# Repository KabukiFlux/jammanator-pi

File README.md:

# Raspberry pi jamma bard "jammanator"

<b align="center">Jammanator, the Raspberry Pi JAMMA output board 
for your cabinet</b>

## Table of contents

- [Why](#why)
- [Description](#description)
- [Schematics](#schematics)
- [Install](#install)
- [Pics and final result](#pics-and-final-result)

## Why?

This was done during some live events on Twitch.tv and tested for some time.

This is a very old design for Raspberry Pi 3B+, 4, 400, it no longer 
has the status that anybody can make money and make profit of it 
so I decided to publish it, if you have an arcade cabinet with JAMMA
a spare Raspberry Pi 3B+ or 4 and you want to have something running
then is a matter of burning the rgbpiOS or the recalboxOS and you have
everything you need to make it work.

## Description

This board is intended to be a PCB used with a Raspberry Pi and a 4x4 5v fan
to remove some heat from the CPU.

This board uses 2 I2C parallel expansion I/O chips connected to the JAMMA
connector in order to map automatically the buttons to the cabinet with no
configuration required.

A voltmeter has been added to check the 5v rail while running.

A protection circuit has been mapped to all the inputs and an extra buffer
to avoid any loss of the I2C bus, if the I2C bus is lost the Raspberry will 
no longer boot the OS (yellow led) this design will avoid that.

In the BOM directory there's an interactive BOM with all the required components.

In the gerbers directory we have the gerbers to manufacture the boards.

In the KiCAD folder we can find the KiCAD project itself.

In the circuit_js folder you can find the simulation for the I/O protection.

## Schematics

This is the schematics.

## Install

If you use a Raspberry Pi 400 (the one with the keyboard) I recommend this
board and the extender in order to use it (check carefully the connector position):

- [GPIO board](https://www.amazon.es/IBest-Waveshare-Raspberry-Color-Coded-Expansion/dp/B08SK71PB4)

- [Extension cable](https://www.amazon.es/vhbw-extensi%C3%B3n-compatible-Raspberry-miniordenador/dp/B0B94KRZ8Z)

Ensure the RP400 pin is in the right position, as the RP400 cannot be powered
via the GPIO we must provide USB-C power and avoid sending power to the GPIO.

1- Send to manufacture the GERBER board to [JLCPCB](https://jlcpcb.com/) or other PCB manufacturer.

2- Get the components required, you can see here the Bill Of Materials [BOM](bom/ibom.html)

3- Solder the components.

4- Connect a Raspberry Pi with [rgbpi-OS](https://ko-fi.com/s/4119fb48b8) or 
[recalbox-OS](https://www.recalbox.com/es/download/stable/rpi/)

5- Follow the installation guide and instructions for the selected OS. 

Once finished you should have something like this:

### Pics and final result

I'm not responsible
============
And yes, read below, no liability is assumed for misuse.

DISCLAIMER (See Licensing)
==========================
See LICENSE fo more information.

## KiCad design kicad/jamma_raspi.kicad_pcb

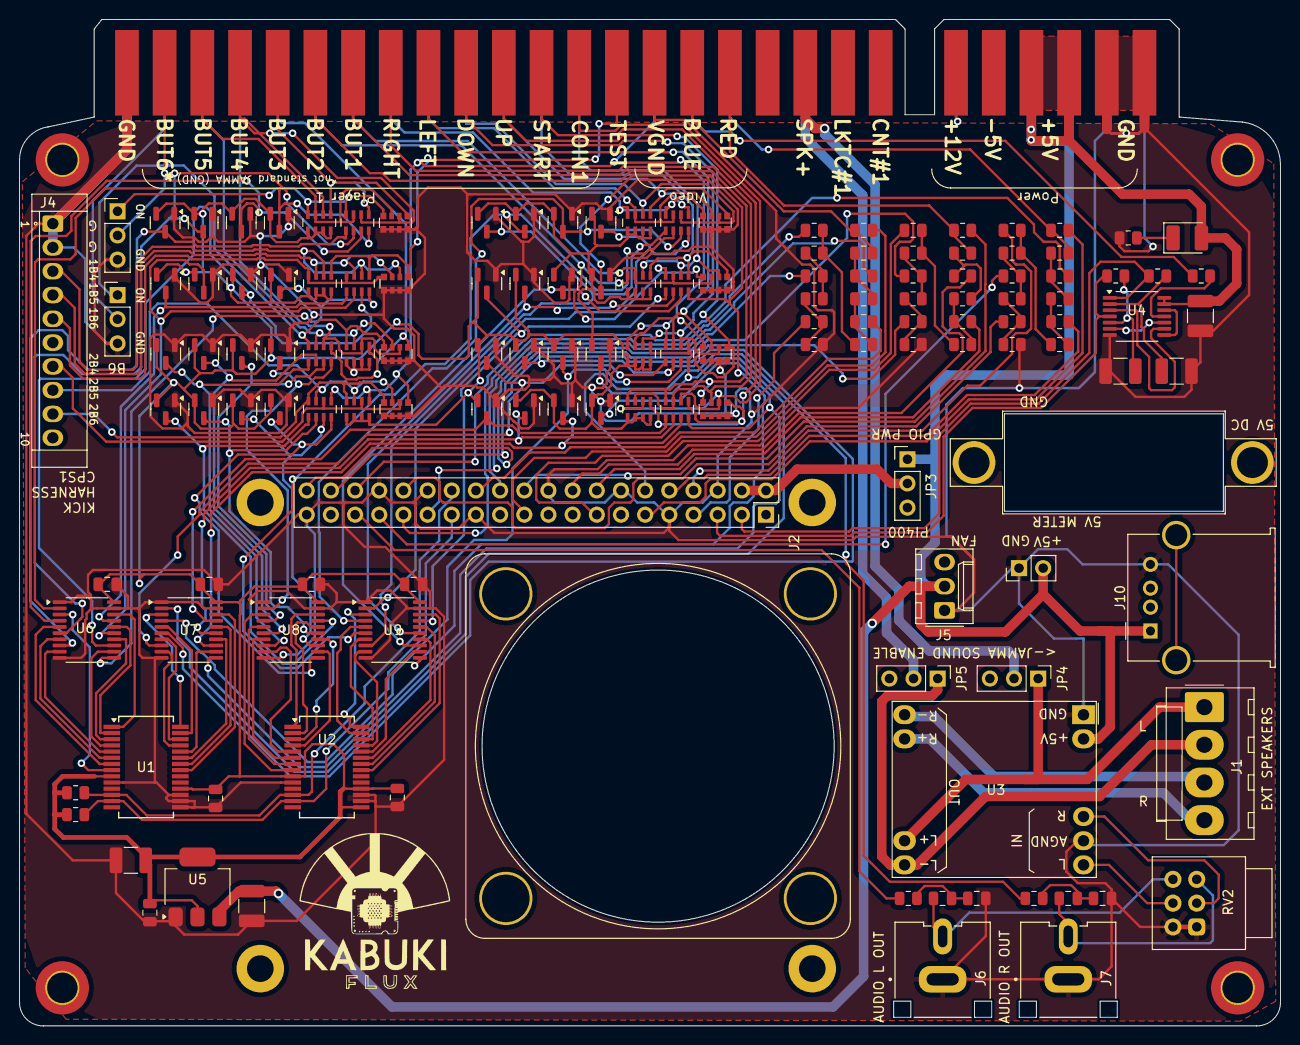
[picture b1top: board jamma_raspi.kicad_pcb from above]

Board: 2 copper layers, 132.5 x 105.7 mm, 149 parts (1 on the bottom side), 165 nets.

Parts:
C1, C4, C16, C17, C18, C50, C51, C52, C53: 0.1u; C_0805_2012Metric
C2, C3: 470n; C_0805_2012Metric
C10, C11, C12, C13, C15: 10u; C_1210_3225Metric_Pad1.33x2.70mm_HandSolder
CN1, CN2, CN3, CN4, CN5, CN6, CN7, CN8: 100n; C_Array_Convex_4x0612
D1, D2, D3, D4, D5, D6, D7, D8, D9, D10, D11, D12, D13, D14, D15, D16, D17, D18, D19, D20, D21, D22, D23, D24, D25, D26, D27, D28, D29, D30, D31, D32: BAT54S; SOT-23
DPWR1: LED RED; LED_1210_3225Metric_Pad1.42x2.65mm_HandSolder
FAN1: Noctua_NF-A4x10_40mm
G1: LOGO; LogoKabuki_18mm
G2: LOGO; LogoKabuki
J1: SPEAKER_STEREO MOLEX396; Molex_KK-396_A-41791-0004_1x04_P3.96mm_Vertical
J2: CONN_02X20; GPIO_2x20_P2.54mm_Vertical_Tall_w_Standoffs
J3: JAMMA_edge
J4: Kick Harness (CPS1 pinout); B10P-SHF-1AA
J5: FAN_5v; Molex_KK-254_AE-6410-03A_1x03_P2.54mm_Vertical
J6: AUDIO L OUT; CUI_RCJ-043
J7: AUDIO R OUT; CUI_RCJ-043
J10: RP400_USB; USB_A_Molex_67643_Horizontal
JP1: 1P_B6_CHAMMA_JAMMA; PinHeader_1x03_P2.54mm_Vertical
JP2: 2P_B6_CHAMMA_JAMMA; PinHeader_1x03_P2.54mm_Vertical
JP3: PI_400_DISCONNECT; PinHeader_1x03_P2.54mm_Vertical
JP4: JAMMA_SPK_DIS_+; PinHeader_1x03_P2.54mm_Vertical
JP5: JAMMA_SPK_DIS_-; PinHeader_1x03_P2.54mm_Vertical
M1, M2, M3, M4: MountingHole_3.2mm_M3_DIN965_Pad_TopBottom
MES1: Voltmeter_DC; PinHeader_1x02_P2.54mm_Vertical
RB1, RB2, RB3, RB4, RB5, RB6: 475; R_0805_2012Metric
RB7, RB8, RB9, RB10, RB11, RB12: 240; R_0805_2012Metric
RG1, RG2, RG3, RG4, RG5, RG6: 475; R_0805_2012Metric
RG7, RG8, RG9, RG10, RG11, RG12: 240; R_0805_2012Metric
RI2C1, RI2C2: 10k; R_0805_2012Metric
RLED1: 1k; R_0805_2012Metric
RN1, RN3, RN5, RN7, RN9, RN11, RN13, RN15: 1k; R_Array_Concave_4x0603
RN2, RN4, RN6, RN8, RN10, RN12, RN14, RN16: 10k; R_Array_Concave_4x0603
RPWM1, RPWM2: 220; R_0805_2012Metric
RR1, RR2, RR3, RR4, RR5, RR6: 475; R_0805_2012Metric
RR7, RR8, RR9, RR10, RR11, RR12: 240; R_0805_2012Metric
RS1, RS2: 4k7; R_0805_2012Metric
RS3: 100; R_0805_2012Metric
RV2: 10k; Potentiometer_Alps_RK097_Dual_Horizontal
U1: MCP23017_SO_PLAYER1; SSOP-28_5.3x10.2mm_P0.65mm
U2: MCP23017_SO_PLAYER2; SSOP-28_5.3x10.2mm_P0.65mm
U3: PAM8403 PCB; PAM8403_module
U4: 74HC86; TSSOP-14_4.4x5mm_P0.65mm
U5: LM1117IMPX-3.3/NOPB; SOT-223-3_TabPin2
U6, U7, U8, U9: SN74LVC244APWR; TSSOP-20_4.4x6.5mm_P0.65mm
VM1: Voltmeter Mechanical; voltmeter

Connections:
+3.3V: C15.1, C16.1, C17.1, C18.1, C50.1, C51.1, C52.1, C53.1, D1.2 (K), D2.2 (K), D3.2 (K), D4.2 (K), D5.2 (K), D6.2 (K), D7.2 (K), D8.2 (K), D9.2 (K), D10.2 (K), D11.2 (K), D12.2 (K), D13.2 (K), D14.2 (K), D15.2 (K), D16.2 (K), D17.2 (K), D18.2 (K), D19.2 (K), D20.2 (K), D21.2 (K), D22.2 (K), D23.2 (K), D24.2 (K), D25.2 (K), D26.2 (K), D27.2 (K), D28.2 (K), D29.2 (K), D30.2 (K), D31.2 (K), D32.2 (K), RI2C1.1, RI2C2.1, RN2.5 (R4.2), RN2.6 (R3.2), RN2.7 (R2.2), RN2.8 (R1.2), RN4.5 (R4.2), RN4.6 (R3.2), RN4.7 (R2.2), RN4.8 (R1.2), RN6.5 (R4.2), RN6.6 (R3.2), RN6.7 (R2.2), RN6.8 (R1.2), RN8.5 (R4.2), RN8.6 (R3.2), RN8.7 (R2.2), RN8.8 (R1.2), RN10.5 (R4.2), RN10.6 (R3.2), RN10.7 (R2.2), RN10.8 (R1.2), RN12.5 (R4.2), RN12.6 (R3.2), RN12.7 (R2.2), RN12.8 (R1.2), RN14.5 (R4.2), RN14.6 (R3.2), RN14.7 (R2.2), RN14.8 (R1.2), RN16.5 (R4.2), RN16.6 (R3.2), RN16.7 (R2.2), RN16.8 (R1.2), U1.9 (VDD), U1.18 (~RESET), U2.9 (VDD), U2.15 (A0), U2.18 (~RESET), U5.2 (VO), U6.20 (VCC), U7.20 (VCC), U8.20 (VCC), U9.20 (VCC)
+5V: C12.1, C13.1, DPWR1.2 (A), J3.3 (+5V), J3.4 (+5V), J3.C (+5V), J3.D (+5V), J5.2, J10.1 (VBUS), JP3.1 (A), MES1.2 (+), U3.2 (VCC), U4.13, U4.14 (VCC), U5.3 (VI)
+12V: J3.6 (+12V), J3.F (+12V)
/B2: J2.7, RB6.1
/B3: J2.29, RB5.1
/B4: J2.31, RB4.1
/B5: J2.26, RB3.1
/B6: J2.24, RB2.1
/B7: J2.21, RB1.1
/BLANKING: U4.8, U4.12
/CSYNC: J3.P (Video_Sync), RS3.1
/G2: J2.32, RG6.1
/G3: J2.33, RG5.1
/G4: J2.8, RG4.1
/G5: J2.10, RG3.1
/G6: J2.36, RG2.1
/G7: J2.11, RG1.1
/HSYNC: J2.5, RS2.2, U4.4
/I2C_SCL: J2.28, RI2C2.2, U1.12 (SCK), U2.12 (SCK)
/I2C_SDA: J2.27, RI2C1.2, U1.13 (SDA), U2.13 (SDA)
/JAMMA RASPI IOs/INPUT01: D1.3 (COM), RN1.8 (R1.2), U6.2 (I0a)
/JAMMA RASPI IOs/INPUT02: D2.3 (COM), RN1.7 (R2.2), U6.4 (I1a)
/JAMMA RASPI IOs/INPUT03: D3.3 (COM), RN1.6 (R3.2), U6.6 (I2a)
/JAMMA RASPI IOs/INPUT04: D4.3 (COM), RN1.5 (R4.2), U6.8 (I3a)
/JAMMA RASPI IOs/INPUT05: D5.3 (COM), RN3.8 (R1.2), U6.11 (I0b)
/JAMMA RASPI IOs/INPUT06: D6.3 (COM), RN3.7 (R2.2), U6.13 (I1b)
/JAMMA RASPI IOs/INPUT07: D7.3 (COM), RN3.6 (R3.2), U6.15 (I2b)
/JAMMA RASPI IOs/INPUT08: D8.3 (COM), RN3.5 (R4.2), U6.17 (I3b)
/JAMMA RASPI IOs/INPUT11: D9.3 (COM), RN5.8 (R1.2), U7.2 (I0a)
/JAMMA RASPI IOs/INPUT12: D10.3 (COM), RN5.7 (R2.2), U7.4 (I1a)
/JAMMA RASPI IOs/INPUT13: D11.3 (COM), RN5.6 (R3.2), U7.6 (I2a)
/JAMMA RASPI IOs/INPUT14: D12.3 (COM), RN5.5 (R4.2), U7.8 (I3a)
/JAMMA RASPI IOs/INPUT15: D13.3 (COM), RN7.8 (R1.2), U7.11 (I0b)
/JAMMA RASPI IOs/INPUT16: D14.3 (COM), RN7.7 (R2.2), U7.13 (I1b)
/JAMMA RASPI IOs/INPUT17: D15.3 (COM), RN7.6 (R3.2), U7.15 (I2b)
/JAMMA RASPI IOs/INPUT18: D16.3 (COM), RN7.5 (R4.2), U7.17 (I3b)
/JAMMA RASPI IOs/INPUT21: D17.3 (COM), RN9.8 (R1.2), U8.2 (I0a)
/JAMMA RASPI IOs/INPUT22: D18.3 (COM), RN9.7 (R2.2), U8.4 (I1a)
/JAMMA RASPI IOs/INPUT23: D19.3 (COM), RN9.6 (R3.2), U8.6 (I2a)
/JAMMA RASPI IOs/INPUT24: D20.3 (COM), RN9.5 (R4.2), U8.8 (I3a)
/JAMMA RASPI IOs/INPUT25: D21.3 (COM), RN11.8 (R1.2), U8.11 (I0b)
/JAMMA RASPI IOs/INPUT26: D22.3 (COM), RN11.7 (R2.2), U8.13 (I1b)
/JAMMA RASPI IOs/INPUT27: D23.3 (COM), RN11.6 (R3.2), U8.15 (I2b)
/JAMMA RASPI IOs/INPUT28: D24.3 (COM), RN11.5 (R4.2), U8.17 (I3b)
/JAMMA RASPI IOs/INPUT31: D25.3 (COM), RN13.8 (R1.2), U9.2 (I0a)
/JAMMA RASPI IOs/INPUT32: D26.3 (COM), RN13.7 (R2.2), U9.4 (I1a)
/JAMMA RASPI IOs/INPUT33: D27.3 (COM), RN13.6 (R3.2), U9.6 (I2a)
/JAMMA RASPI IOs/INPUT34: D28.3 (COM), RN13.5 (R4.2), U9.8 (I3a)
/JAMMA RASPI IOs/INPUT35: D29.3 (COM), RN15.8 (R1.2), U9.11 (I0b)
/JAMMA RASPI IOs/INPUT36: D30.3 (COM), RN15.7 (R2.2), U9.13 (I1b)
/JAMMA RASPI IOs/INPUT37: D31.3 (COM), RN15.6 (R3.2), U9.15 (I2b)
/JAMMA RASPI IOs/INPUT38: D32.3 (COM), RN15.5 (R4.2), U9.17 (I3b)
/L: C2.1, J6.1 (In), RV2.6
/P1_B1: U1.27 (GPA6), U7.5 (O2b)
/P1_B1_J: CN4.3 (R3.1), J3.22 (Player_1_Button_1), RN7.3 (R3.1), RN8.3 (R3.1)
/P1_B2: U1.28 (GPA7), U7.3 (O3b)
/P1_B2_J: CN4.4 (R4.1), J3.23 (Player_1_Button_2), RN7.4 (R4.1), RN8.4 (R4.1)
/P1_B3: U1.1 (GPB0), U6.18 (O0a)
/P1_B3_J: CN1.1 (R1.1), J3.24 (Player_1_Button_3), RN1.1 (R1.1), RN2.1 (R1.1)
/P1_B4: U1.2 (GPB1), U6.16 (O1a)
/P1_B4_J: CN1.2 (R2.1), J3.25 (Player_1_Button_4), RN1.2 (R2.1), RN2.2 (R2.1)
/P1_B5: U1.3 (GPB2), U6.14 (O2a)
/P1_B5_J: CN1.3 (R3.1), J3.26 (Player_1_Button_5), RN1.3 (R3.1), RN2.3 (R3.1)
/P1_B6: U1.4 (GPB3), U6.12 (O3a)
/P1_B6_J: J3.27 (GND/P1_Button_6), JP1.2 (C)
/P1_B6_J_C: CN1.4 (R4.1), JP1.1 (A), RN1.4 (R4.1), RN2.4 (R4.1)
/P1_COIN: U1.26 (GPA5), U7.7 (O1b)
/P1_COIN_J: CN4.2 (R2.1), J3.16 (Coin_1), RN7.2 (R2.1), RN8.2 (R2.1)
/P1_DOWN: U1.22 (GPA1), U7.16 (O1a)
/P1_DOWN_J: CN3.2 (R2.1), J3.19 (Player_1_Down), RN5.2 (R2.1), RN6.2 (R2.1)
/P1_K4: U1.6 (GPB5), U6.7 (O1b)
/P1_K4_K: CN2.2 (R2.1), J4.3, RN3.2 (R2.1), RN4.2 (R2.1)
/P1_K5: U1.7 (GPB6), U6.5 (O2b)
/P1_K5_K: CN2.3 (R3.1), J4.4, RN3.3 (R3.1), RN4.3 (R3.1)
/P1_K6: U1.8 (GPB7), U6.3 (O3b)
/P1_K6_K: CN2.4 (R4.1), J4.5, RN3.4 (R4.1), RN4.4 (R4.1)
/P1_LEFT: U1.23 (GPA2), U7.14 (O2a)
/P1_LEFT_J: CN3.3 (R3.1), J3.20 (Player_1_Left), RN5.3 (R3.1), RN6.3 (R3.1)
/P1_RIGHT: U1.24 (GPA3), U7.12 (O3a)
/P1_RIGHT_J: CN3.4 (R4.1), J3.21 (Player_1_Right), RN5.4 (R4.1), RN6.4 (R4.1)
/P1_START: U1.25 (GPA4), U7.9 (O0b)
/P1_START_J: CN4.1 (R1.1), J3.17 (Player_1_Start), RN7.1 (R1.1), RN8.1 (R1.1)
/P1_UP: U1.21 (GPA0), U7.18 (O0a)
/P1_UP_J: CN3.1 (R1.1), J3.18 (Player_1_Up), RN5.1 (R1.1), RN6.1 (R1.1)
/P2_B1: U2.27 (GPA6), U9.5 (O2b)
/P2_B1_J: CN8.3 (R3.1), J3.Z (Player_2_Button_1), RN15.3 (R3.1), RN16.3 (R3.1)
/P2_B2: U2.28 (GPA7), U9.3 (O3b)
/P2_B2_J: CN8.4 (R4.1), J3.a (Player_2_Button_2), RN15.4 (R4.1), RN16.4 (R4.1)
/P2_B3: U2.1 (GPB0), U8.18 (O0a)
/P2_B3_J: CN5.1 (R1.1), J3.b (Player_2_Button_3), RN9.1 (R1.1), RN10.1 (R1.1)
/P2_B4: U2.2 (GPB1), U8.16 (O1a)
/P2_B4_J: CN5.2 (R2.1), J3.c (Player_2_Button_4), RN9.2 (R2.1), RN10.2 (R2.1)
/P2_B5: U2.3 (GPB2), U8.14 (O2a)
/P2_B5_J: CN5.3 (R3.1), J3.d (Player_2_Button_5), RN9.3 (R3.1), RN10.3 (R3.1)
/P2_B6: U2.4 (GPB3), U8.12 (O3a)
/P2_B6_J: J3.e (GND/P2_Button_6), JP2.2 (C)
/P2_B6_J_C: CN5.4 (R4.1), JP2.1 (A), RN9.4 (R4.1), RN10.4 (R4.1)
/P2_COIN: U2.26 (GPA5), U9.7 (O1b)
/P2_COIN_J: CN8.2 (R2.1), J3.T (Coin_2), RN15.2 (R2.1), RN16.2 (R2.1)
/P2_DOWN: U2.22 (GPA1), U9.16 (O1a)
/P2_DOWN_J: CN7.2 (R2.1), J3.W (Player_2_Down), RN13.2 (R2.1), RN14.2 (R2.1)
/P2_K4: U2.6 (GPB5), U8.7 (O1b)
/P2_K4_K: CN6.2 (R2.1), J4.7, RN11.2 (R2.1), RN12.2 (R2.1)
/P2_K5: U2.7 (GPB6), U8.5 (O2b)
/P2_K5_K: CN6.3 (R3.1), J4.8, RN11.3 (R3.1), RN12.3 (R3.1)
/P2_K6: U2.8 (GPB7), U8.3 (O3b)
/P2_K6_K: CN6.4 (R4.1), J4.9, RN11.4 (R4.1), RN12.4 (R4.1)
/P2_LEFT: U2.23 (GPA2), U9.14 (O2a)
/P2_LEFT_J: CN7.3 (R3.1), J3.X (Player_2_Left), RN13.3 (R3.1), RN14.3 (R3.1)
/P2_RIGHT: U2.24 (GPA3), U9.12 (O3a)
/P2_RIGHT_J: CN7.4 (R4.1), J3.Y (Player_2_Right), RN13.4 (R4.1), RN14.4 (R4.1)
/P2_START: U2.25 (GPA4), U9.9 (O0b)
/P2_START_J: CN8.1 (R1.1), J3.U (Player_2_Start), RN15.1 (R1.1), RN16.1 (R1.1)
/P2_UP: U2.21 (GPA0), U9.18 (O0a)
/P2_UP_J: CN7.1 (R1.1), J3.V (Player_2_Up), RN13.1 (R1.1), RN14.1 (R1.1)
/PI_PWR: J2.2, J2.4, JP3.2 (C)
/PWM_LEFT: J2.35, RPWM2.1
/PWM_RIGHT: J2.12, RPWM1.1
/R: C3.1, J7.1 (In), RV2.3
/R2: J2.38, RR6.1
/R3: J2.40, RR5.1
/R4: J2.15, RR4.1
/R5: J2.16, RR3.1
/R6: J2.18, RR2.1
/R7: J2.22, RR1.1
/RGB_BLUE: J3.13 (Video_Blue), RB1.2, RB12.1
/RGB_GREEN: J3.N (Video_Green), RG1.2, RG12.1
/RGB_RED: J3.12 (Video_Red), RR1.2, RR12.1
/SERVICE: U2.5 (GPB4), U8.9 (O0b)
/SERVICE_J: CN6.1 (R1.1), J3.R (Service), RN11.1 (R1.1), RN12.1 (R1.1)
/SPK_L+: J1.1, JP4.1 (A), U3.7 (L_OUT+)
/SPK_L+_J: J3.10 (Speaker+/R), JP4.2 (C)
/SPK_L-: J1.2, JP5.1 (A), U3.6 (L_OUT-)
/SPK_L-_J: J3.L (Speaker-/L), JP5.2 (C)
/SPK_R+: J1.4, U3.8 (R_OUT+)
/SPK_R-: J1.3, U3.9 (R_OUT-)
/TEST: U1.5 (GPB4), U6.9 (O0b)
/TEST_J: CN2.1 (R1.1), J3.15 (Test), RN3.1 (R1.1), RN4.1 (R1.1)
/VSYNC: J2.3, RS1.2, U4.1
GND: C1.2, C4.2, C10.2, C11.2, C12.2, C13.2, C15.2, C16.2, C17.2, C18.2, C50.2, C51.2, C52.2, C53.2, CN1.5 (R4.2), CN1.6 (R3.2), CN1.7 (R2.2), CN1.8 (R1.2), CN2.5 (R4.2), CN2.6 (R3.2), CN2.7 (R2.2), CN2.8 (R1.2), CN3.5 (R4.2), CN3.6 (R3.2), CN3.7 (R2.2), CN3.8 (R1.2), CN4.5 (R4.2), CN4.6 (R3.2), CN4.7 (R2.2), CN4.8 (R1.2), CN5.5 (R4.2), CN5.6 (R3.2), CN5.7 (R2.2), CN5.8 (R1.2), CN6.5 (R4.2), CN6.6 (R3.2), CN6.7 (R2.2), CN6.8 (R1.2), CN7.5 (R4.2), CN7.6 (R3.2), CN7.7 (R2.2), CN7.8 (R1.2), CN8.5 (R4.2), CN8.6 (R3.2), CN8.7 (R2.2), CN8.8 (R1.2), D1.1 (A), D2.1 (A), D3.1 (A), D4.1 (A), D5.1 (A), D6.1 (A), D7.1 (A), D8.1 (A), D9.1 (A), D10.1 (A), D11.1 (A), D12.1 (A), D13.1 (A), D14.1 (A), D15.1 (A), D16.1 (A), D17.1 (A), D18.1 (A), D19.1 (A), D20.1 (A), D21.1 (A), D22.1 (A), D23.1 (A), D24.1 (A), D25.1 (A), D26.1 (A), D27.1 (A), D28.1 (A), D29.1 (A), D30.1 (A), D31.1 (A), D32.1 (A), J2.6, J2.9, J2.14, J2.20, J2.25, J2.30, J2.34, J2.39, J3.1 (GND), J3.2 (GND), J3.14 (Video_Gnd), J3.28 (GND), J3.A (GND), J3.B (GND), J3.f (GND), J4.1, J4.2, J5.1, J6.2 (Ext), J7.2 (Ext), J10.4 (GND), JP1.3 (B), JP2.3 (B), MES1.1 (-), RB7.2, RG7.2, RLED1.2, RR7.2, RV2.1, RV2.4, U1.10 (VSS), U1.15 (A0), U1.16 (A1), U1.17 (A2), U2.10 (VSS), U2.16 (A1), U2.17 (A2), U3.1 (GND), U3.4 (GND_AUDIO_IN), U4.7 (GND), U5.1 (GND), U6.1 (OEa), U6.10 (GND), U6.19 (OEb), U7.1 (OEa), U7.10 (GND), U7.19 (OEb), U8.1 (OEa), U8.10 (GND), U8.19 (OEb), U9.1 (OEa), U9.10 (GND), U9.19 (OEb)
unnamed: C1.1, C3.2, RPWM1.2
unnamed: C2.2, C4.1, RPWM2.2
unnamed: C10.1, RS1.1, U4.2
unnamed: C11.1, RS2.1, U4.5
unnamed: DPWR1.1 (K), RLED1.1
unnamed: RB5.2, RB8.1, RB9.2
unnamed: RB6.2, RB7.1, RB8.2
unnamed: RB3.2, RB10.1, RB11.2
unnamed: RB4.2, RB9.1, RB10.2
unnamed: RB2.2, RB11.1, RB12.2
unnamed: RG5.2, RG8.1, RG9.2
unnamed: RG6.2, RG7.1, RG8.2
unnamed: RG3.2, RG10.1, RG11.2
unnamed: RG4.2, RG9.1, RG10.2
unnamed: RG2.2, RG11.1, RG12.2
unnamed: RR5.2, RR8.1, RR9.2
unnamed: RR6.2, RR7.1, RR8.2
unnamed: RR3.2, RR10.1, RR11.2
unnamed: RR4.2, RR9.1, RR10.2
unnamed: RR2.2, RR11.1, RR12.2
unnamed: RS3.2, U4.11
unnamed: RV2.5, U3.5 (L_AUDIO_IN)
unnamed: RV2.2, U3.3 (R_AUDIO_IN)
unnamed: U4.3, U4.9
unnamed: U4.6, U4.10

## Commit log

2025-02-17 JAMMANATOR™ upload and publish
